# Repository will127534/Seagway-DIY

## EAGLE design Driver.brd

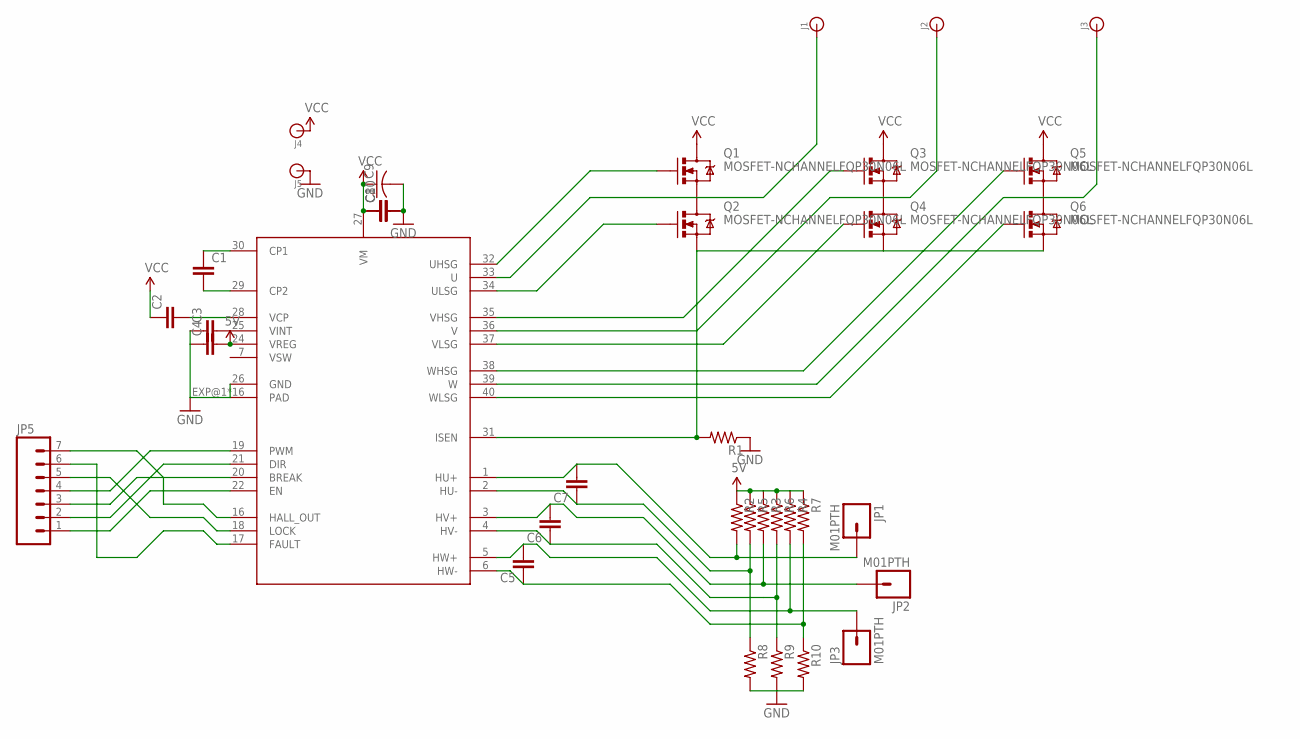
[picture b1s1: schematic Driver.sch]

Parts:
C1, C2, C3, C4, C8: CAP1206; 1206
C5, C6, C7, C10: CAP0805; 0805
C9: CAP_POLPTH4; CPOL-RADIAL-1000UF-25V
J1, J2, J3, J4, J5: BANANA_CONN
JP1, JP2, JP3: M01PTH; 1X01
JP5: M07; 1X07
Q1, Q2, Q3, Q4, Q5, Q6: MOSFET-NCHANNELFQP30N06L; TO220V
R1: RESISTOR2010; R2010
R2, R3, R4, R5, R6, R7, R8, R9, R10: RESISTOR0805-RES; 0805
U$1: DRV8307; QFN40-6X6

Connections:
5V: C4.2, R2.1, R3.1, R4.1, R5.1, R6.1, R7.1, U$1.24 (VREG)
GND: C3.1, C4.1, C8.2, C9.-, C10.2, J5.P$1, R1.1, R8.2, R9.2, R10.2, U$1.26 (GND), U$1.EXP@1 (PAD), U$1.EXP@2 (PAD), U$1.EXP@3 (PAD), U$1.EXP@4 (PAD), U$1.EXP@5 (PAD), U$1.EXP@6 (PAD), U$1.EXP@7 (PAD), U$1.EXP@8 (PAD), U$1.EXP@9 (PAD), U$1.EXP@10 (PAD), U$1.EXP@11 (PAD), U$1.EXP@12 (PAD), U$1.EXP@13 (PAD), U$1.EXP@14 (PAD), U$1.EXP@15 (PAD), U$1.EXP@16 (PAD)
unnamed: C1.1, U$1.30 (CP1)
unnamed: C1.2, U$1.29 (CP2)
unnamed: C2.2, U$1.28 (VCP)
unnamed: C3.2, U$1.25 (VINT)
unnamed: JP5.4, U$1.19 (PWM)
unnamed: Q2.1 (G), U$1.34 (ULSG)
unnamed: J1.P$1, Q1.3 (S), Q2.2 (D), U$1.33 (U)
unnamed: J2.P$1, Q3.3 (S), Q4.2 (D), U$1.36 (V)
unnamed: J3.P$1, Q5.3 (S), Q6.2 (D), U$1.39 (W)
unnamed: Q1.1 (G), U$1.32 (UHSG)
unnamed: Q3.1 (G), U$1.35 (VHSG)
unnamed: Q4.1 (G), U$1.37 (VLSG)
unnamed: Q5.1 (G), U$1.38 (WHSG)
unnamed: Q2.3 (S), Q4.3 (S), Q6.3 (S), R1.2, U$1.31 (ISEN)
unnamed: Q6.1 (G), U$1.40 (WLSG)
unnamed: C5.2, JP3.1, R4.2, U$1.5 (HW+)
unnamed: C5.1, R7.2, R10.1, U$1.6 (HW-)
unnamed: C6.2, JP2.1, R3.2, U$1.3 (HV+)
unnamed: C6.1, R6.2, R9.1, U$1.4 (HV-)
unnamed: C7.2, JP1.1, R2.2, U$1.1 (HU+)
unnamed: C7.1, R5.2, R8.1, U$1.2 (HU-)
unnamed: JP5.2, U$1.21 (DIR)
unnamed: JP5.3, U$1.20 (BREAK)
unnamed: JP5.1, U$1.22 (EN)
unnamed: JP5.7, U$1.16 (HALL_OUT)
unnamed: JP5.5, U$1.18 (LOCK)
unnamed: JP5.6, U$1.17 (FAULT)
VCC: C2.1, C8.1, C9.+, C10.1, J4.P$1, Q1.2 (D), Q3.2 (D), Q5.2 (D), U$1.27 (VM)

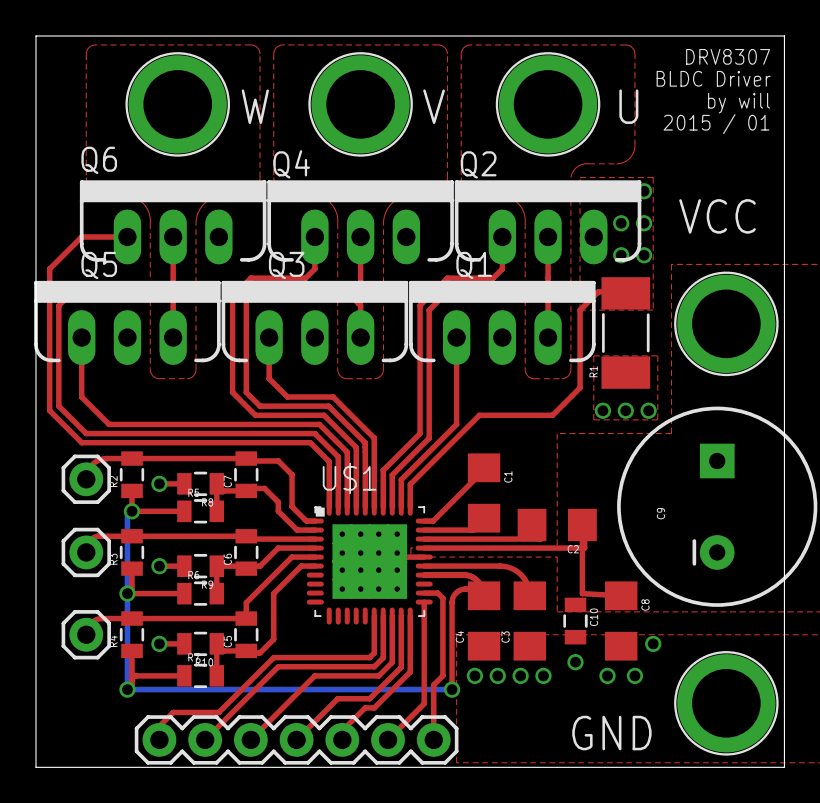
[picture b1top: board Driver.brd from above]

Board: 2 copper layers, 41.6 x 40.6 mm, 36 parts (0 on the bottom side), 30 nets.

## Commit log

2015-01-30 Ver 1.0
    DRV8307 Driver Board

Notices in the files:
parts and their libraries:
SparkFun-Capacitors: Licensing: Creative Commons ShareAlike 4.0 International - https://creativecommons.org/licenses/by-sa/4.0
